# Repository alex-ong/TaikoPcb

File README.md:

Simple taiko pcb based on  https://github.com/ShikyC/Taiko-Drum-Controller-Arduino

It uses a ESP32 S3 Supermini

Pcb:

Render:

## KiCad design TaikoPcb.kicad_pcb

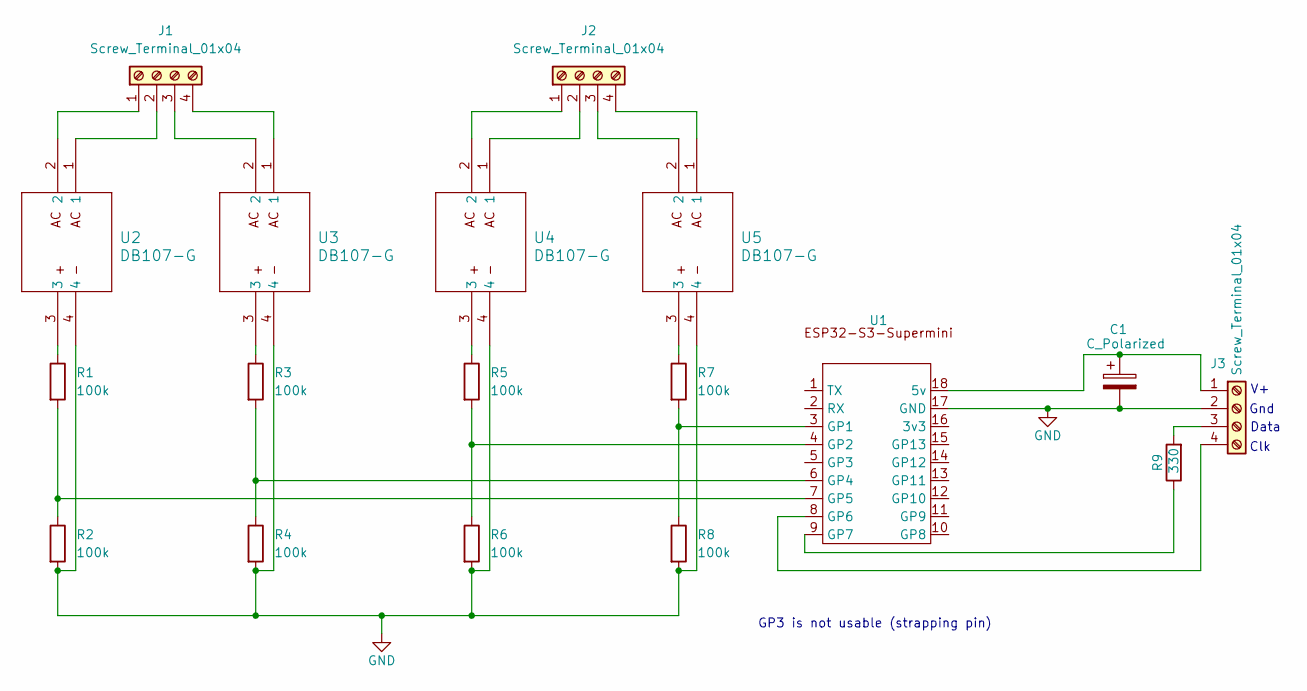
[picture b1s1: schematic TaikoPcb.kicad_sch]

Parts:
C1: C_Polarized; D_DO-34_SOD68_P10.16mm_Horizontal
J1, J2, J3: Screw_Terminal_01x04; TerminalBlock_Xinya_XY308-2.54-4P_1x04_P2.54mm_Horizontal
R1, R2, R3, R4, R5, R6, R7, R8: 100k; R_Axial_DIN0207_L6.3mm_D2.5mm_P7.62mm_Horizontal
R9: 330; R_Axial_DIN0207_L6.3mm_D2.5mm_P7.62mm_Horizontal
U1: ESP32-S3-Supermini; esp32-s3-supermini
U2, U3, U4, U5: DB107-G; DB107-G_CIP

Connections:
GND: C1.2, J3.2, R2.2, R4.2, R6.2, R8.2, U1.17 (GND), U2.4, U3.4, U4.4, U5.4
unnamed: J1.1, U2.2
unnamed: J1.2, U2.1
unnamed: J1.3, U3.2
unnamed: J1.4, U3.1
unnamed: J2.1, U4.2
unnamed: J2.2, U4.1
unnamed: J2.3, U5.2
unnamed: J2.4, U5.1
unnamed: C1.1, J3.1, U1.18 (5v)
unnamed: J3.3, R9.2
unnamed: J3.4, U1.8 (GP6)
unnamed: R1.1, U2.3
unnamed: R3.1, U3.3
unnamed: R5.1, U4.3
unnamed: R7.1, U5.3
unnamed: R7.2, R8.1, U1.3 (GP1)
unnamed: R5.2, R6.1, U1.4 (GP2)
unnamed: R3.2, R4.1, U1.6 (GP4)
unnamed: R1.2, R2.1, U1.7 (GP5)
unnamed: R9.1, U1.9 (GP7)

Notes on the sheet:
Data
GP3 is not usable (strapping pin)
Clk
Gnd

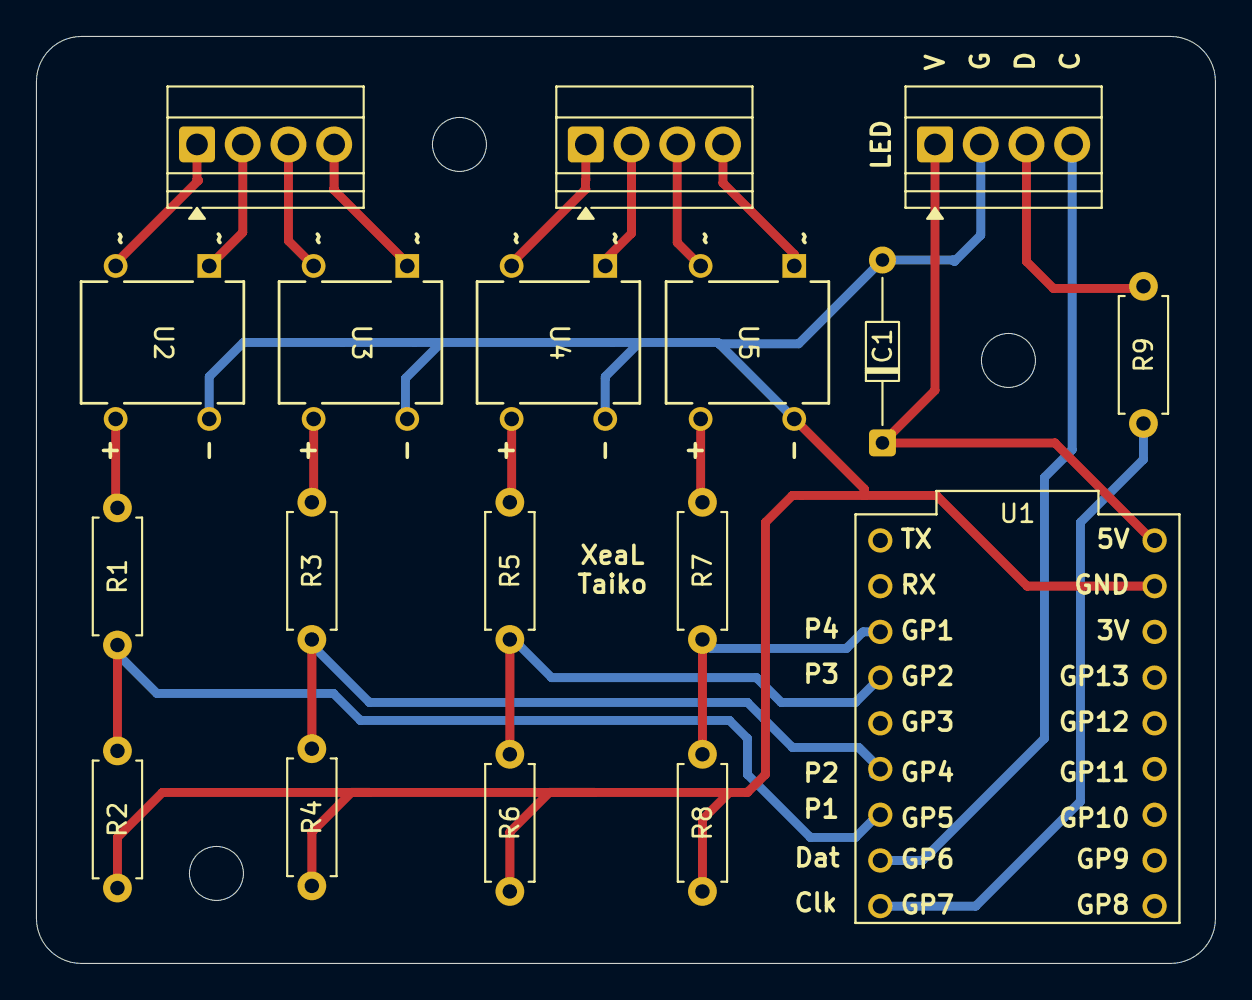
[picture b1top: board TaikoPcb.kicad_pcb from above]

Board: 2 copper layers, 65.5 x 51.5 mm, 18 parts (0 on the bottom side), 21 nets.

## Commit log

2025-11-06 Empty project
2025-11-07 Add schematic
2025-11-07 Add supermini footprint
2025-11-07 rewire
2025-11-14 fill in most of PCB
2025-11-14 Adjust so that usbc plug can fit
2025-11-16 More adjustments
2025-11-16 Add gerbers and screenshots
2025-11-16 Add new lines
2025-11-16 New gerbers, remove jlcjlcjlcjlc
